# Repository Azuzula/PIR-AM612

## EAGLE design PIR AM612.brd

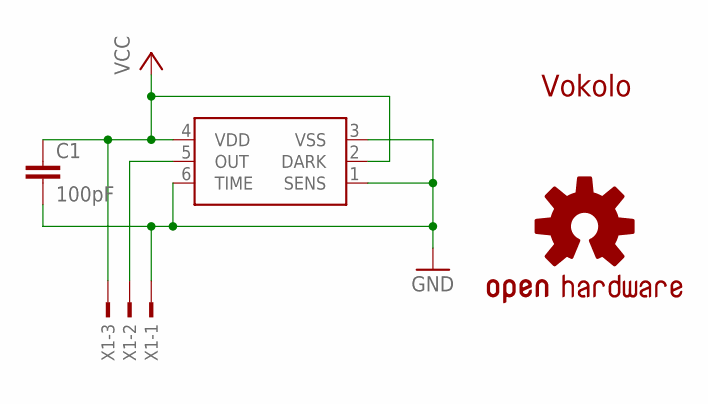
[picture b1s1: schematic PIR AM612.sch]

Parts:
C1: 100pF; C0603
LOGO1: OSHW-LOGOS; OSHW-LOGO-S
U$2: AM612; TO5
U$3: LOGO_VOKOLO9,7MM; LOGO_VOKOLO_8MM
X1: TSW-103-07-G-S; TSW-103-XX-G-S

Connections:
GND: C1.2, U$2.1 (SENS), U$2.3 (VSS), U$2.6 (TIME), X1.1
unnamed: U$2.5 (OUT), X1.2
VCC: C1.1, U$2.2 (DARK), U$2.4 (VDD), X1.3

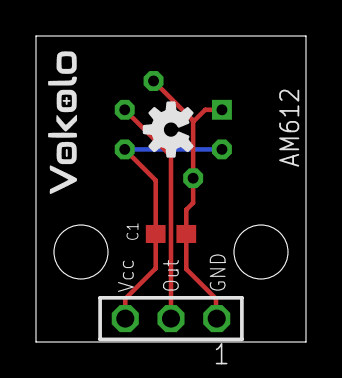
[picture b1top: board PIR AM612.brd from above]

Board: 2 copper layers, 15.0 x 17.0 mm, 5 parts (1 on the bottom side), 3 nets.

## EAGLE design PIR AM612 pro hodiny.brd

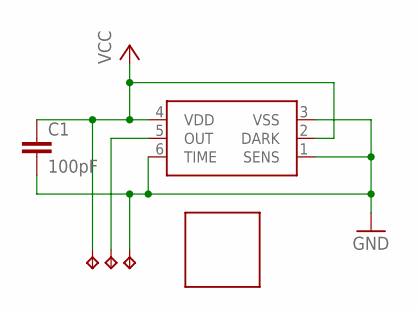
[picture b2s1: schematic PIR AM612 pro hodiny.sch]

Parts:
C1: 100pF; C0603
TP1, TP2, TP3: TPB1,27; B1,27
U$1: AM612; TO5
U$2: LOGO_VOKOLO7,5MM; LOGO_VOKOLO_6,2MM

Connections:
GND: C1.2, TP3.TP, U$1.1 (SENS), U$1.3 (VSS), U$1.6 (TIME)
unnamed: TP2.TP, U$1.5 (OUT)
VCC: C1.1, TP1.TP, U$1.2 (DARK), U$1.4 (VDD)

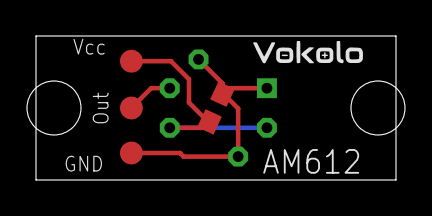
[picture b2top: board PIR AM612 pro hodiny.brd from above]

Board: 2 copper layers, 20.0 x 8.0 mm, 6 parts (1 on the bottom side), 3 nets.

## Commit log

2023-10-09 Add files via upload
    Small PIR AM612 breakout board and slim version for my NeoPixSegment clock.
2023-10-09 Add files via upload
    Gerber files for both small and slim breakout board.

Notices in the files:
parts and their libraries:
SparkFun-Aesthetics: Licensing: Creative Commons ShareAlike 4.0 International - https://creativecommons.org/licenses/by-sa/4.0
